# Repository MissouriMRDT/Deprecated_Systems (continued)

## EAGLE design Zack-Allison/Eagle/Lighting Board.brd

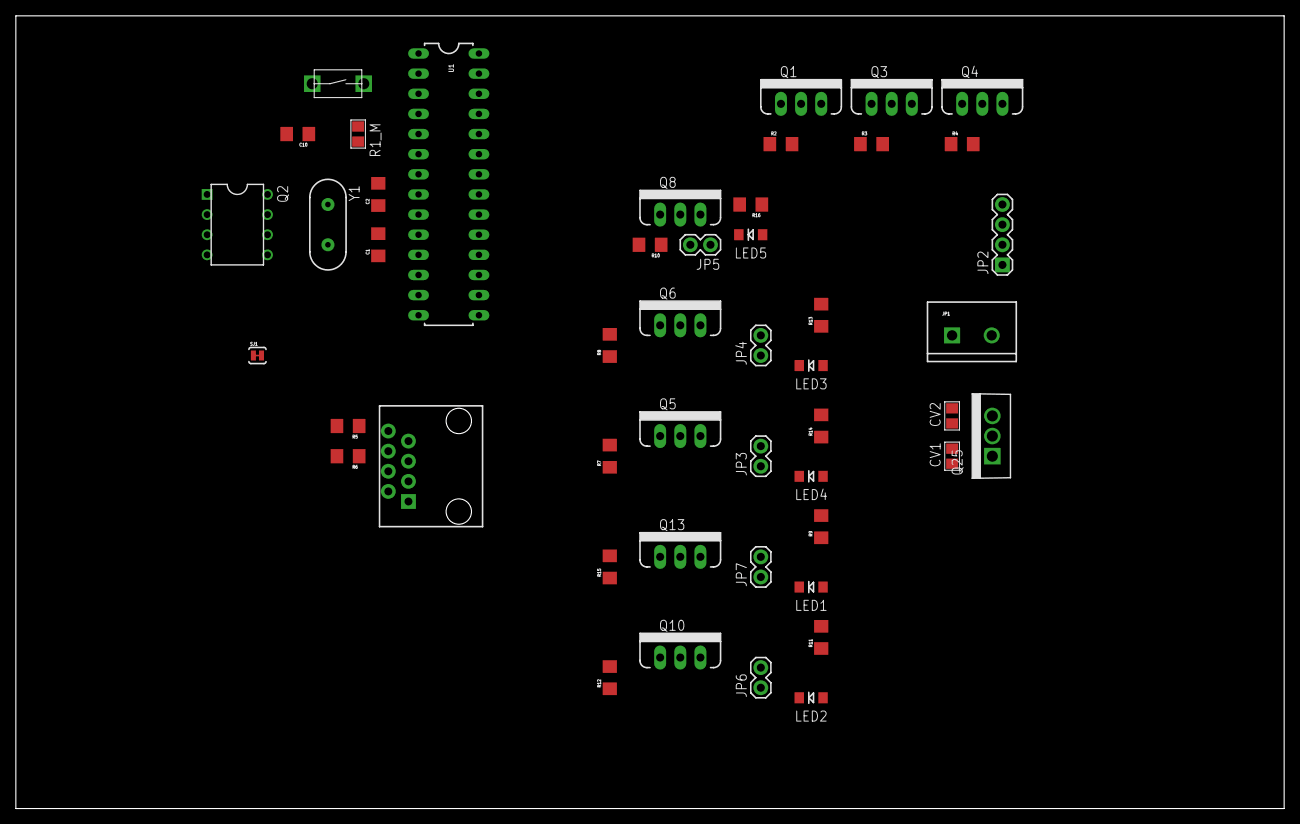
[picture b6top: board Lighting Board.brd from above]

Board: 2 copper layers, 160.0 x 100.0 mm, 48 parts (0 on the bottom side), 34 nets, no tracks yet.

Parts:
C1, C2: 0.1uF; 1206
C10: .1uF; 1206
CV1, CV2: C_0805
JP1: M025MM; SCREWTERMINAL-5MM-2
JP2: 1X04
JP3, JP4, JP5, JP6, JP7: M02PTH; 1X02
LED1, LED2, LED3, LED4, LED5: LED-1206
MS: J_MC32857; J_TOGGLE
Q1, Q3, Q4, Q5, Q6, Q8, Q10, Q13: MOSFET-NCHANNELFQP30N06L; TO220V
Q2: Q_LTC490; DIP8
Q25: LDO; TO-220
R1_M: 200; R_0805
R2, R3, R4, R7, R8, R10, R12, R15: 1k; 1206
R5, R6: 120 Ohm; 1206
R9, R11: 1206
R13, R14, R16: 200; 1206
SJ1: SOLDERJUMPERTRACE; SJ_2S-TRACE
U1: ATMEGA328P_PDIP; DIL28-3
U$1: RJ45-8PTH; RJ45-8
Y1: HC49US

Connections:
D1: Q10.1, R12.2, U1.13
D2: Q13.1, R15.2, U1.14
GND: C1.2, C2.2, C10.2, CV1.2, CV2.2, JP1.2, MS.P$1, Q1.3, Q2.4, Q3.3, Q4.3, Q5.3, Q6.3, Q8.3, Q10.3, Q13.3, Q25.2, R2.1, R3.1, R4.1, R7.1, R8.1, R10.1, R12.1, R15.1, SJ1.1, U1.8, U1.22
unnamed: Q2.5, R6.2, U$1.1
unnamed: C2.1, U1.10, Y1.1
unnamed: LED1.A, R9.1
unnamed: LED2.A, R11.1
unnamed: LED3.A, R13.1
unnamed: LED4.A, R14.1
unnamed: LED5.A, R16.1
unnamed: Q2.6, R6.1, U$1.2
unnamed: Q2.7, R5.2, U$1.6
unnamed: Q2.8, R5.1, U$1.3
unnamed: SJ1.2, U$1.7, U$1.8
unnamed: C1.1, U1.9, Y1.2
unnamed: JP2.2, Q1.2
unnamed: JP2.3, Q3.2
unnamed: JP2.4, Q4.2
unnamed: MS.P$2, R1_M.1, U1.1
N%2: JP4.2, LED3.C, Q6.2
N%3: JP3.2, LED4.C, Q5.2
N%106: JP5.2, LED5.C, Q8.2
N%107: JP6.2, LED2.C, Q10.2
N%110: JP7.2, LED1.C, Q13.2
PWM1: Q3.1, R3.2, U1.5
PWM2: Q4.1, R4.2, U1.11
PWM3: Q1.1, R2.2, U1.12
PWM4: Q5.1, R7.2, U1.15
PWM5: Q6.1, R8.2, U1.16
PWM6: Q8.1, R10.2, U1.17
RXD: Q2.2, U1.2
TXD: Q2.3, U1.3
V5: C10.1, CV2.1, Q2.1, Q25.3, R1_M.2, U1.7, U1.20
VIN: CV1.1, JP1.1, JP2.1, JP3.1, JP4.1, JP5.1, JP6.1, JP7.1, Q25.1, R9.2, R11.2, R13.2, R14.2, R16.2

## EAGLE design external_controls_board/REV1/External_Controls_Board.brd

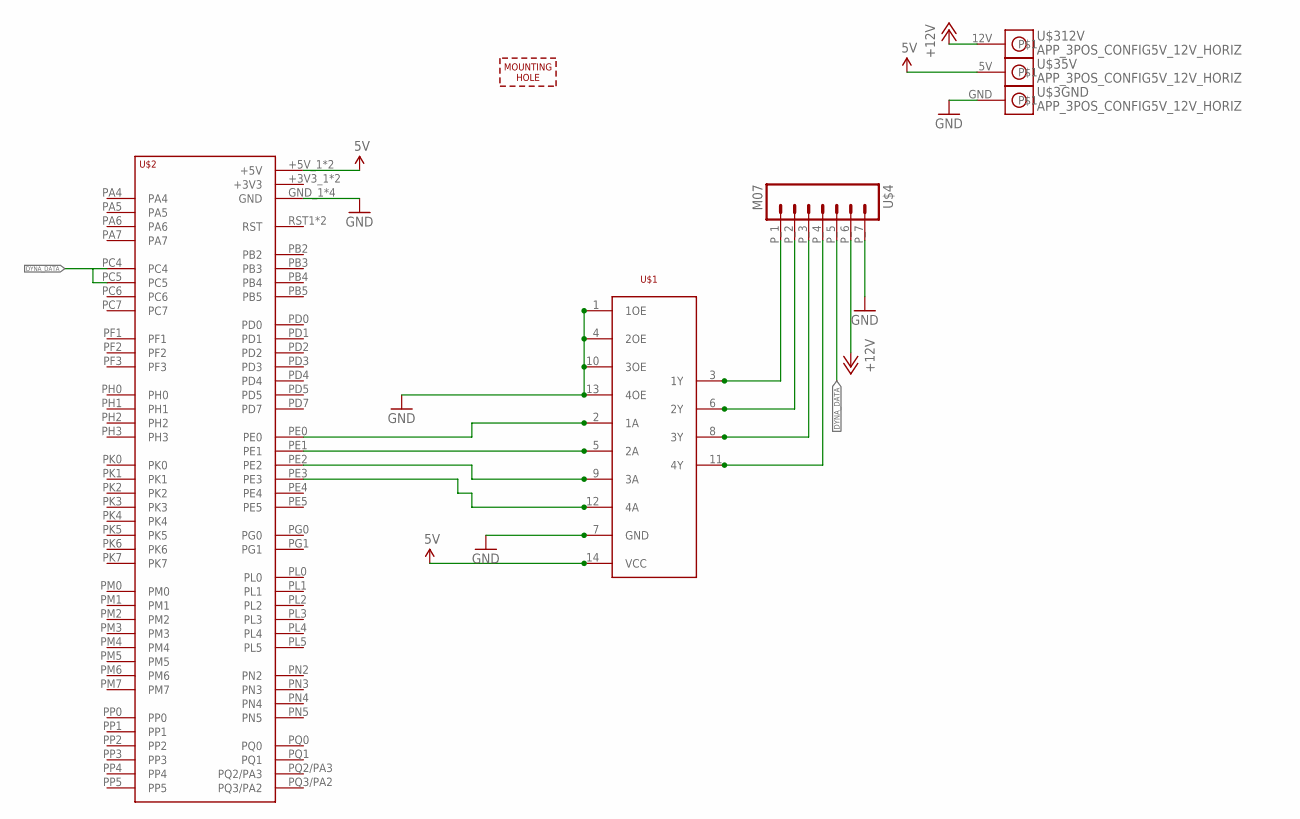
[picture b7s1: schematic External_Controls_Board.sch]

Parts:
U$1: SN74AHCT125; SOIC14
U$2: TIVA-C-CONNECTED
U$3: APP_3POS_CONFIG5V_12V_HORIZ; APP45_5V_12V_HORIZ_CONFIG
U$4: M07; MOLEX_43650-07
U$6: MOUNTING_HOLE#8; #8_SCREW

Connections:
+5V: U$1.14 (VCC), U$2.+5V_1 (+5V), U$2.+5V_2 (+5V), U$3.5V
+12V: U$3.12V, U$4.P_6 (6)
DYNA_DATA: U$2.PC4, U$2.PC5, U$4.P_5 (5)
GND: U$1.1 (1OE), U$1.4 (2OE), U$1.7 (GND), U$1.10 (3OE), U$1.13 (4OE), U$2.GND_1 (GND), U$2.GND_2 (GND), U$2.GND_3 (GND), U$2.GND_4 (GND), U$3.GND, U$4.P_7 (7)
PWM0_3.3: U$1.12 (4A), U$2.PE3
PWM0_5: U$1.11 (4Y), U$4.P_4 (4)
PWM1_3.3: U$1.9 (3A), U$2.PE2
PWM1_5: U$1.8 (3Y), U$4.P_3 (3)
PWM2_3.3: U$1.5 (2A), U$2.PE1
PWM2_5: U$1.6 (2Y), U$4.P_2 (2)
PWM3_3.3: U$1.2 (1A), U$2.PE0
PWM3_5: U$1.3 (1Y), U$4.P_1 (1)

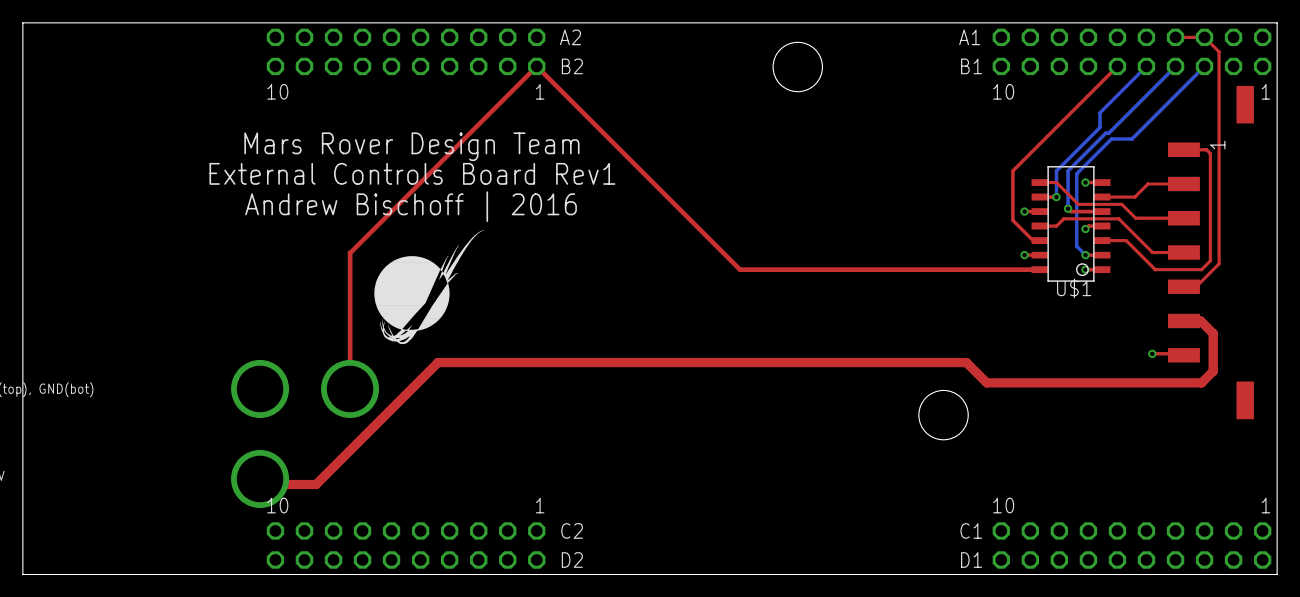
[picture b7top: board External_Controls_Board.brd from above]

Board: 2 copper layers, 109.7 x 48.3 mm, 7 parts (0 on the bottom side), 12 nets.

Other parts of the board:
U$5: MOUNTING_HOLE#8; #8_SCREW
U$7: MRDT_LOGO

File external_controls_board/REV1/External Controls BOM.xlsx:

Already Own? | Device | Details | Quantity | Link
 | SN74AHCT125 - Logic Level Shifter | SOIC14 package | 1.0 | http://www.digikey.com/product-detail/en/SN74AHCT125DR/296-4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
 | Tica C Connected |  | 1.0 | http://www.newark.com/texas-instruments/ek-tm4c1294xl/evalua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
 | APP_3POS_CONFIG5V_12V_HORIZ | 1 RED, 1 YELLOW, 1 BLACK | 3.0
 | Molex MicroFit 3.0 - 7POS male | WM2459CT-ND | 2.0 | http://www.digikey.com/product-detail/en/43650-0712/WM2459CT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
 | #8 SCREW | Mounting hole for M6 bolt. | 2.0
 | through hole female pin header 2x10 | S6106-ND | 4.0 | http://www.digikey.com/product-detail/en/PPPC102LFBN-RC/S610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
